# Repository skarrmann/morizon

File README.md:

# Morizon Keyboard

Morizon is a 5-row version of the Horizon keyboard.

This project is a direct modification of the Horizon project. The schematic and PCBs have been modified to support this 5-row layout.

As with Horizon, two separate PCB designs are available in the [`gerbers`](gerbers) folder: one for MX switches (19mm x 19mm spacing), and one for Choc switches (18mm x 17mm spacing).

Please refer to the [Horizon keyboard repository](https://github.com/skarrmann/horizon) for project documentation. Only Morizon-specific details are noted below!

## Keyboard firmware

* [QMK](https://github.com/qmk/qmk_firmware/tree/master/keyboards/morizon)
* ZMK
    * Morizon shield definition is in [skarrmann's zmk-config](https://github.com/skarrmann/zmk-config)

## Bill of materials

Same as the [Horizon keyboard BOM](https://github.com/skarrmann/horizon/#bill-of-materials), but you will also need:

* Morizon PCBs (instead of Horizon PCBs)
* 14 more keyswitches
* 14 more keycaps
* 14 more 1N4148 SOD-123 diodes
* 1 more M2 6mm screw
* 1 more M2 nut

## Revision History

* **Rev1** (2022-02-05)
    * PCB: Create MX and Choc boards with bottom and top plates (based on Horizon).
    * Schematic: Wire as 66 key 10x7 matrix.
* **Rev1.1** (2022-03-21)
    * PCB, Schematic: No physical changes. Files upgraded to KiCad 6, and Gerber files regenerated using Horizon Board Producer 2.3.
* **Rev1.2** (2023-11-09)
    * PCB, Schematic: No physical changes. Files upgraded to KiCad 7, and Gerber files regenerated using Horizon Board Producer 2.4.

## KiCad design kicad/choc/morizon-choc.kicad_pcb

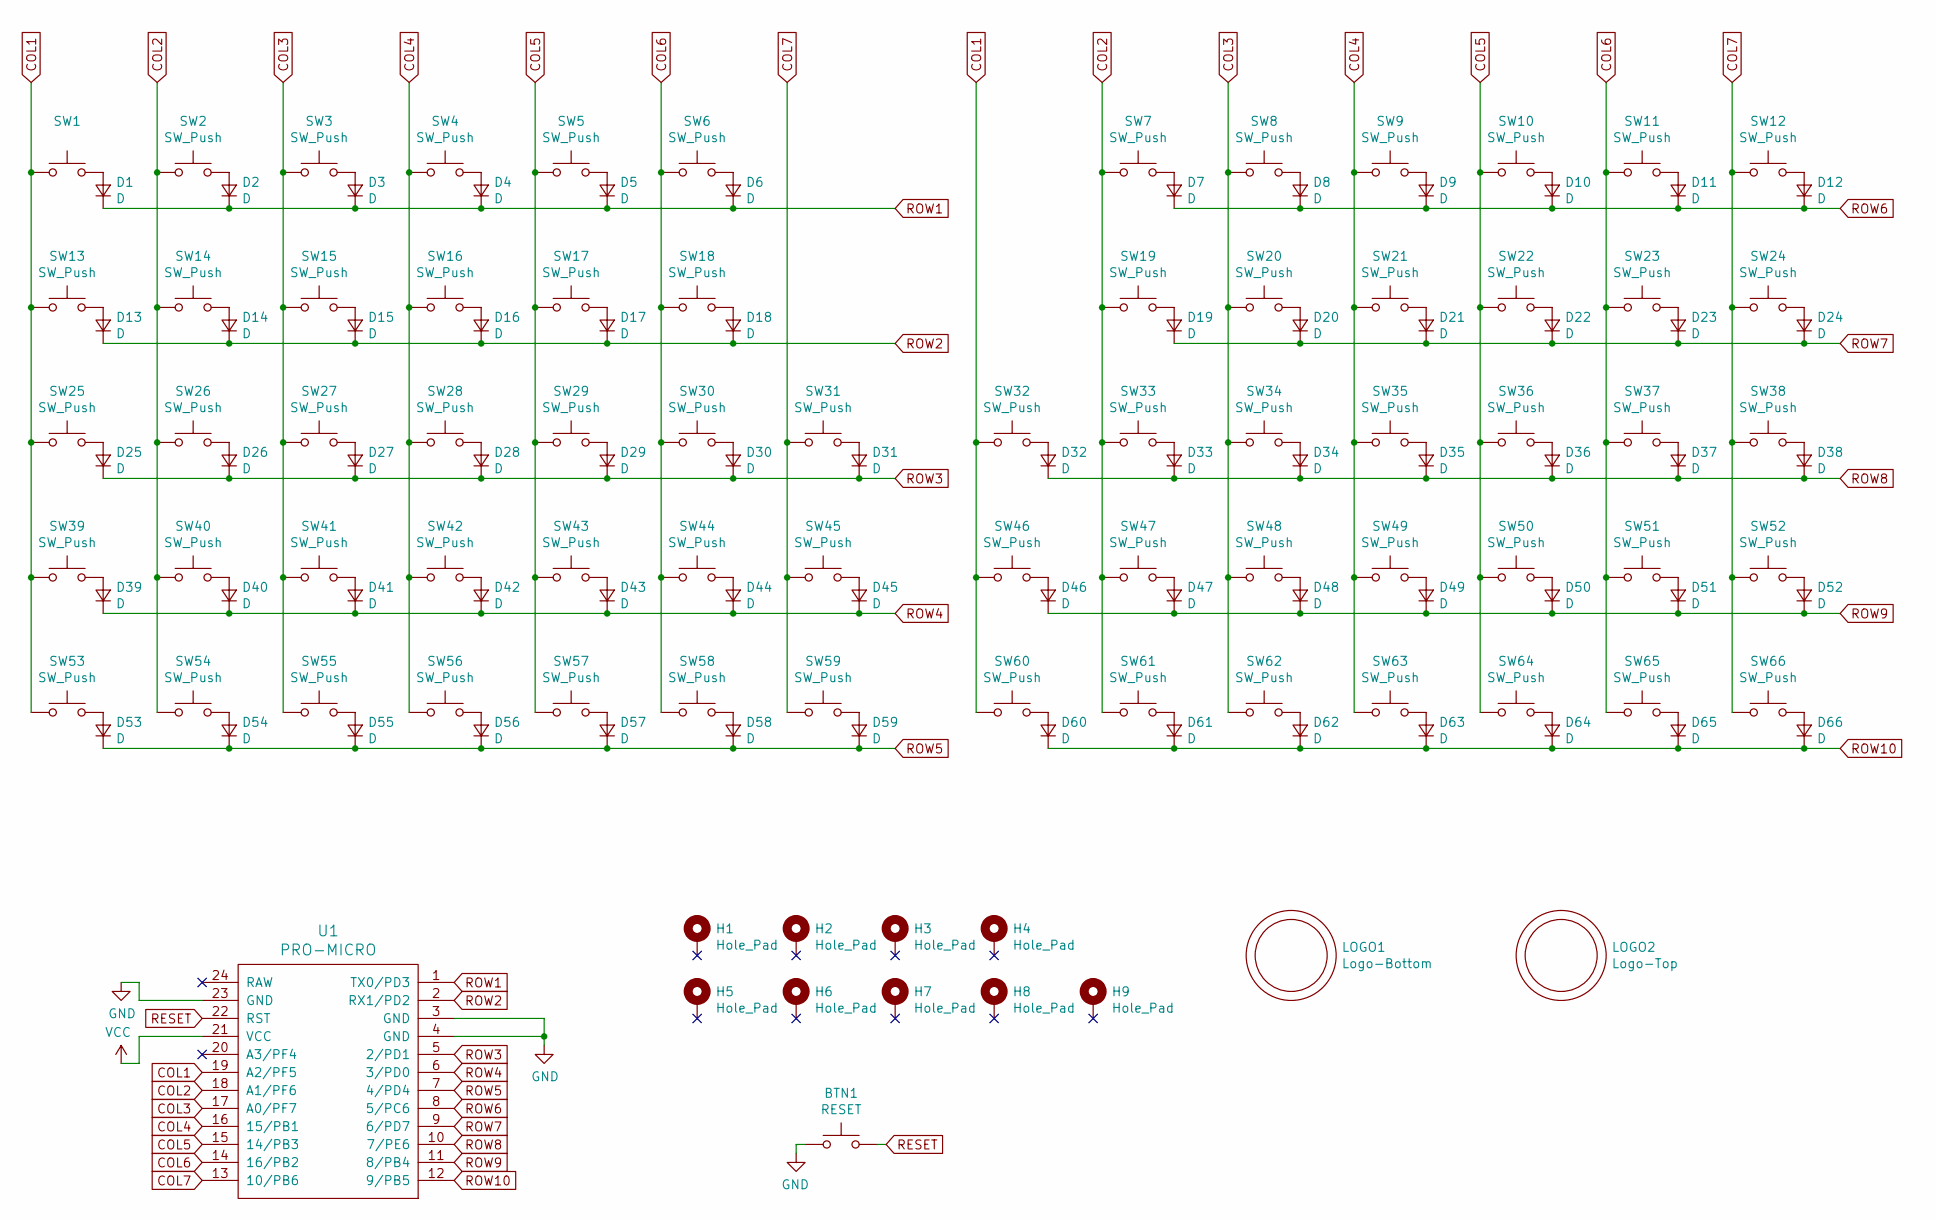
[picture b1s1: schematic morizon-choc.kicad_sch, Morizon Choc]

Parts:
BTN1: RESET; SW_Push_6mm
D1, D2, D3, D4, D5, D6, D7, D8, D9, D10, D11, D12, D13, D14, D15, D16, D17, D18, D19, D20, D21, D22, D23, D24, D25, D26, D27, D28, D29, D30, D31, D32, D33, D34, D35, D36, D37, D38, D39, D40, D41, D42, D43, D44, D45, D46, D47, D48, D49, D50, D51, D52, D53, D54, D55, D56, D57, D58, D59, D60, D61, D62, D63, D64, D65, D66: D; D_SOD-123
H1, H2, H3, H4, H5, H6, H7, H8, H9: Hole_Pad; Mount_M2
LOGO1: Logo-Bottom; Logo_Morizon_Small
LOGO2: Logo-Top; Logo_Morizon_M
SW1: (no value)
SW2, SW3, SW4, SW5, SW6, SW7, SW8, SW9, SW10, SW11, SW12, SW13, SW14, SW15, SW16, SW17, SW18, SW19, SW20, SW21, SW22, SW23, SW24, SW25, SW26, SW27, SW28, SW29, SW30, SW31, SW32, SW33, SW34, SW35, SW36, SW37, SW38, SW39, SW40, SW41, SW42, SW43, SW44, SW45, SW46, SW47, SW48, SW49, SW50, SW51, SW52, SW53, SW54, SW55, SW56, SW57, SW58, SW59, SW60, SW61, SW62, SW63, SW64, SW65, SW66: SW_Push; SW_Choc
U1: PRO-MICRO; Pro-Micro

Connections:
COL1: SW1.1, SW13.1, SW25.1, SW32.1, SW39.1, SW46.1, SW53.1, SW60.1, U1.19 (A2/PF5)
COL2: SW2.1, SW7.1, SW14.1, SW19.1, SW26.1, SW33.1, SW40.1, SW47.1, SW54.1, SW61.1, U1.18 (A1/PF6)
COL3: SW3.1, SW8.1, SW15.1, SW20.1, SW27.1, SW34.1, SW41.1, SW48.1, SW55.1, SW62.1, U1.17 (A0/PF7)
COL4: SW4.1, SW9.1, SW16.1, SW21.1, SW28.1, SW35.1, SW42.1, SW49.1, SW56.1, SW63.1, U1.16 (15/PB1)
COL5: SW5.1, SW10.1, SW17.1, SW22.1, SW29.1, SW36.1, SW43.1, SW50.1, SW57.1, SW64.1, U1.15 (14/PB3)
COL6: SW6.1, SW11.1, SW18.1, SW23.1, SW30.1, SW37.1, SW44.1, SW51.1, SW58.1, SW65.1, U1.14 (16/PB2)
COL7: SW12.1, SW24.1, SW31.1, SW38.1, SW45.1, SW52.1, SW59.1, SW66.1, U1.13 (10/PB6)
GND: BTN1.2, U1.3 (GND), U1.4 (GND), U1.23 (GND)
unnamed: D1.2 (A), SW1.2
unnamed: D2.2 (A), SW2.2
unnamed: D3.2 (A), SW3.2
unnamed: D4.2 (A), SW4.2
unnamed: D5.2 (A), SW5.2
unnamed: D6.2 (A), SW6.2
unnamed: D7.2 (A), SW7.2
unnamed: D8.2 (A), SW8.2
unnamed: D9.2 (A), SW9.2
unnamed: D10.2 (A), SW10.2
unnamed: D11.2 (A), SW11.2
unnamed: D12.2 (A), SW12.2
unnamed: D13.2 (A), SW13.2
unnamed: D14.2 (A), SW14.2
unnamed: D15.2 (A), SW15.2
unnamed: D16.2 (A), SW16.2
unnamed: D17.2 (A), SW17.2
unnamed: D18.2 (A), SW18.2
unnamed: D19.2 (A), SW19.2
unnamed: D20.2 (A), SW20.2
unnamed: D21.2 (A), SW21.2
unnamed: D22.2 (A), SW22.2
unnamed: D23.2 (A), SW23.2
unnamed: D24.2 (A), SW24.2
unnamed: D25.2 (A), SW25.2
unnamed: D26.2 (A), SW26.2
unnamed: D27.2 (A), SW27.2
unnamed: D28.2 (A), SW28.2
unnamed: D29.2 (A), SW29.2
unnamed: D30.2 (A), SW30.2
unnamed: D31.2 (A), SW31.2
unnamed: D32.2 (A), SW32.2
unnamed: D33.2 (A), SW33.2
unnamed: D34.2 (A), SW34.2
unnamed: D35.2 (A), SW35.2
unnamed: D36.2 (A), SW36.2
unnamed: D37.2 (A), SW37.2
unnamed: D38.2 (A), SW38.2
unnamed: D39.2 (A), SW39.2
unnamed: D40.2 (A), SW40.2
unnamed: D41.2 (A), SW41.2
unnamed: D42.2 (A), SW42.2
unnamed: D43.2 (A), SW43.2
unnamed: D44.2 (A), SW44.2
unnamed: D45.2 (A), SW45.2
unnamed: D46.2 (A), SW46.2
unnamed: D47.2 (A), SW47.2
unnamed: D48.2 (A), SW48.2
unnamed: D49.2 (A), SW49.2
unnamed: D50.2 (A), SW50.2
unnamed: D51.2 (A), SW51.2
unnamed: D52.2 (A), SW52.2
unnamed: D53.2 (A), SW53.2
unnamed: D54.2 (A), SW54.2
unnamed: D55.2 (A), SW55.2
unnamed: D56.2 (A), SW56.2
unnamed: D57.2 (A), SW57.2
unnamed: D58.2 (A), SW58.2
unnamed: D59.2 (A), SW59.2
unnamed: D60.2 (A), SW60.2
unnamed: D61.2 (A), SW61.2
unnamed: D62.2 (A), SW62.2
unnamed: D63.2 (A), SW63.2
unnamed: D64.2 (A), SW64.2
unnamed: D65.2 (A), SW65.2
unnamed: D66.2 (A), SW66.2
RESET: BTN1.1, U1.22 (RST)
ROW1: D1.1 (K), D2.1 (K), D3.1 (K), D4.1 (K), D5.1 (K), D6.1 (K), U1.1 (TX0/PD3)
ROW2: D13.1 (K), D14.1 (K), D15.1 (K), D16.1 (K), D17.1 (K), D18.1 (K), U1.2 (RX1/PD2)
ROW3: D25.1 (K), D26.1 (K), D27.1 (K), D28.1 (K), D29.1 (K), D30.1 (K), D31.1 (K), U1.5 (2/PD1)
ROW4: D39.1 (K), D40.1 (K), D41.1 (K), D42.1 (K), D43.1 (K), D44.1 (K), D45.1 (K), U1.6 (3/PD0)
ROW5: D53.1 (K), D54.1 (K), D55.1 (K), D56.1 (K), D57.1 (K), D58.1 (K), D59.1 (K), U1.7 (4/PD4)
ROW6: D7.1 (K), D8.1 (K), D9.1 (K), D10.1 (K), D11.1 (K), D12.1 (K), U1.8 (5/PC6)
ROW7: D19.1 (K), D20.1 (K), D21.1 (K), D22.1 (K), D23.1 (K), D24.1 (K), U1.9 (6/PD7)
ROW8: D32.1 (K), D33.1 (K), D34.1 (K), D35.1 (K), D36.1 (K), D37.1 (K), D38.1 (K), U1.10 (7/PE6)
ROW9: D46.1 (K), D47.1 (K), D48.1 (K), D49.1 (K), D50.1 (K), D51.1 (K), D52.1 (K), U1.11 (8/PB4)
ROW10: D60.1 (K), D61.1 (K), D62.1 (K), D63.1 (K), D64.1 (K), D65.1 (K), D66.1 (K), U1.12 (9/PB5)

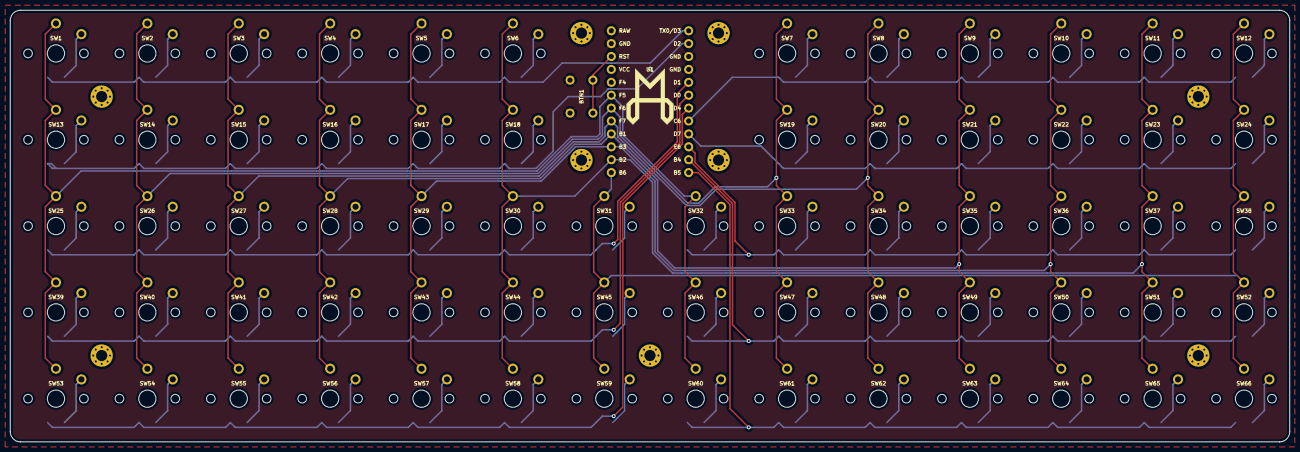
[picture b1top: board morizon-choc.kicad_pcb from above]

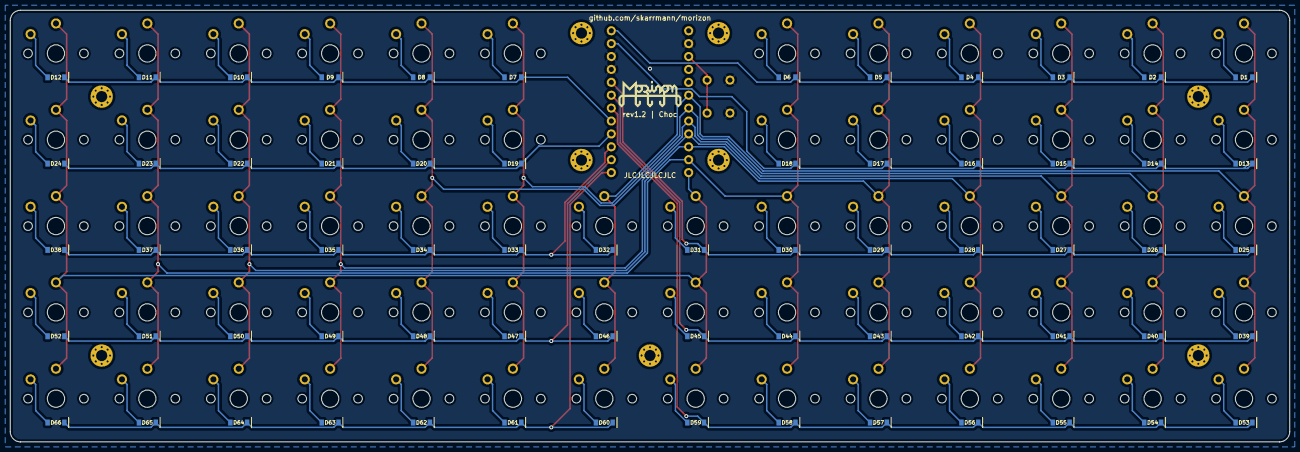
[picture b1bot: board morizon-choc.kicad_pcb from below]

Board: 2 copper layers, 252.0 x 85.0 mm, 145 parts (67 on the bottom side), 85 nets.

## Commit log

2022-02-05 Initial commit copied from Horizon. Update readme and create logo SVGs
2022-02-05 Implement Morizon Choc
2022-02-06 Implement Morizon MX
2022-02-06 Note current status in readme
2022-02-06 Fix typo in readme
2022-02-09 Note final design review is complete
2022-02-10 Note PCBs ordered from JLCPCB
2022-03-02 Note PCBs arrived
2022-03-05 Note keyboard was built and successfully tested.
2022-03-06 Add images to repo. Remove status section since this project is complete except for QMK firmware PR
2022-03-08 Link to official QMK repo (KB definition merged)
2022-03-18 Link to Morizon ZMK firmware
2022-03-21 Upgrade project files to KiCad 6
2022-03-21 Use KiCad 6 symbol library format
2023-11-10 Upgrade project files to KiCad 7
2023-12-20 Remove Horizon board producer plugin (it is manages in Horizon repo)
